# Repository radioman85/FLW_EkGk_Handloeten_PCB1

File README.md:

### Präsentation
[FabLab - Handlötkurs 02-2025.pdf](https://github.com/user-attachments/files/19078771/FabLab.-.Handlotkurs.02-2025.pdf)

### BOM

Currently unavailable

### Programming Pi Pico

## Preparation

1. Download, install and run the [thonny app](https://thonny.org/)
2. Connect the pico
3. In the Thonny app on the right bottom corner you can see your connected pico. From there install the micro python firmware

## Python Script
1. Once the pico has received its micro python firmware click on the "Stop" button on top of the thonny app.
5. Load the script you want to download to the raspi.
6. Go to "Save as", where it asks for either save on PC or on Raspberry (if not asked, the raspberry is not connected correctly (its firmware may not be up-to-date)).
7. Select "Raspberry Pi".
8. Save it as "main.py" (it must be named as "main" else it wont auto-start after reboot)
9. Happy running :-)

### Löten - Ausrüstung

 - Lötkolben (Link: [JBC CD-2BQF](https://shop.electronic-metals.ch/produkte/loettechnik/loetgeraete-ein-kanal/jbc/94951/jbc-kompakt-loetstation-cd-2bqf-wetec-edition?sPartner=10002?number=807278&gad_source=1&gclid=CjwKCAjwx-CyBhAqEiwAeOcTdfXDNTq5UXqakSejQxAiqUnyBB9TK4aIC8MYHQ78THFY60kKdBs1GRoCRy4QAvD_BwE), Handle (included): [T245](https://www.jbctools.com/t245-general-purpose-handle-product-45.html) , Spitzen (NOT included): [C245-030](https://shop.electronic-metals.ch/produkte/loettechnik/loet-entloetspitzen/jbc/c245-fuer-t245/rundform/8647/jbc-loetspitze-serie-c245-rundform?number=801290), -034, -906)
 - Lötzinn + Paste
    - 63% (Sn), 37% (Pb) (Link: [Lötdraht 0.7 mm](https://ch.farnell.com/multicore-loctite/d610scf222-250g/l-tdraht-60-40-0-7mm-250g/dp/454072), Link: [Paste - Chip Quik SMD291AX](https://ch.farnell.com/chip-quik/smd291ax/l-tpaste-no-clean-synthetisch/dp/3549310)) oder
    - 95,5% (Sn), 3,8% (Ag), 0,7% (Cu) (Link: [Lötdraht 0.7 mm](https://ch.farnell.com/multicore-loctite/d96scf222-250g/l-tdraht-105-0-7mm-250g/dp/454590), Link: [Chip Quik TS391SNL](https://ch.farnell.com/chip-quik/ts391snl/l-tpaste-no-clean-synthetisch/dp/3549323))
 - Lötflussmittel (Link: [Chip Quik SMD291](https://www.mouser.ch/ProductDetail/Chip-Quik/SMD291?qs=8BX3xQzFIvmwkympZqnNNA%3D%3D))
 - Lötmatte
 - Pinzetten (Link: [Weller Erem 7SASL, gebogen](https://ch.farnell.com/erem/7sasl/pr-zisionspinzette-gebogen-spitz/dp/2946763), Link: [Weller Erem 3SASL, gerade](https://ch.farnell.com/erem/3sasl/pinzette-120mm/dp/1014352))
 - Zahbüsrteli / Wattestäbli (Link: [M-Budget Zahnbürste](https://www.migros.ch/de/product/mo/96751))
 - Fläschli Isopropanol (Link: [Isopropanol 99,9 %](https://www.gerstaecker.ch/Isopropanol-99-9.html))
 - Shimblade (Link: [EDSYN - ST706](https://ch.farnell.com/edsyn/st706/halter-f-r-entl-tklingen/dp/844457), Ersatzklingen (Link: [EDSYN - RB641](https://ch.farnell.com/edsyn/rb641/entl-tklingen-zuschneidbares-stahlband/dp/844445))
 - Tip Tinner/Cleaner/Activator (Link: [Weller Tip Activater](https://www.simpex.ch/shop/produktionstechnik/loetzubehoer/tip-aktivator-bleifrei/?gad_campaignid=22242456144))

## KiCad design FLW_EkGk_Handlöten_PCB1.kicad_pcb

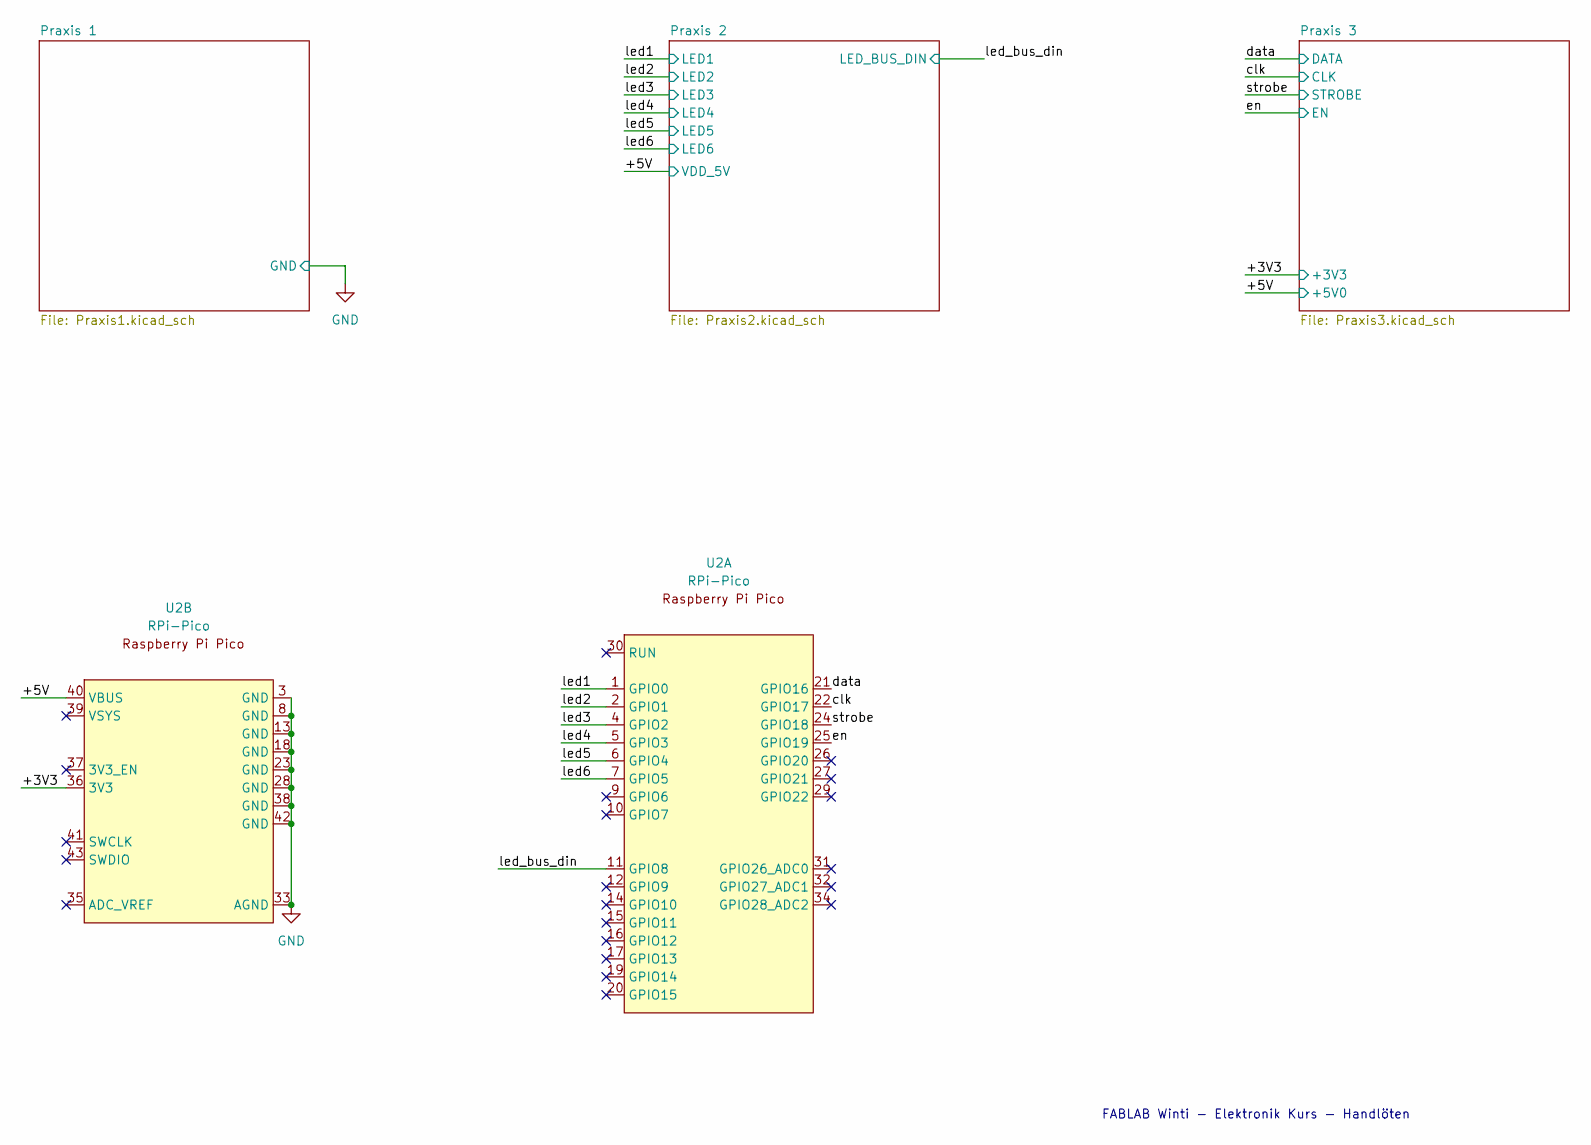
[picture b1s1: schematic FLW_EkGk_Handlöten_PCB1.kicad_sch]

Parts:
U2: RPi-Pico; RPi_Pico_SMD_TH

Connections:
/+3V3: U2.36 (3V3); also elsewhere on the board
/+5V: U2.40 (VBUS); also elsewhere on the board
/clk: U2.22 (GPIO17); also elsewhere on the board
/data: U2.21 (GPIO16); also elsewhere on the board
/en: U2.25 (GPIO19); also elsewhere on the board
/led1: U2.1 (GPIO0); also elsewhere on the board
/led2: U2.2 (GPIO1); also elsewhere on the board
/led3: U2.4 (GPIO2); also elsewhere on the board
/led4: U2.5 (GPIO3); also elsewhere on the board
/led5: U2.6 (GPIO4); also elsewhere on the board
/led6: U2.7 (GPIO5); also elsewhere on the board
/led_bus_din: U2.11 (GPIO8); also elsewhere on the board
/strobe: U2.24 (GPIO18); also elsewhere on the board
GND: U2.3 (GND), U2.8 (GND), U2.13 (GND), U2.18 (GND), U2.23 (GND), U2.28 (GND), U2.33 (AGND), U2.38 (GND), U2.42 (GND); also elsewhere on the board

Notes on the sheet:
FABLAB Winti - Elektronik Kurs - Handlöten

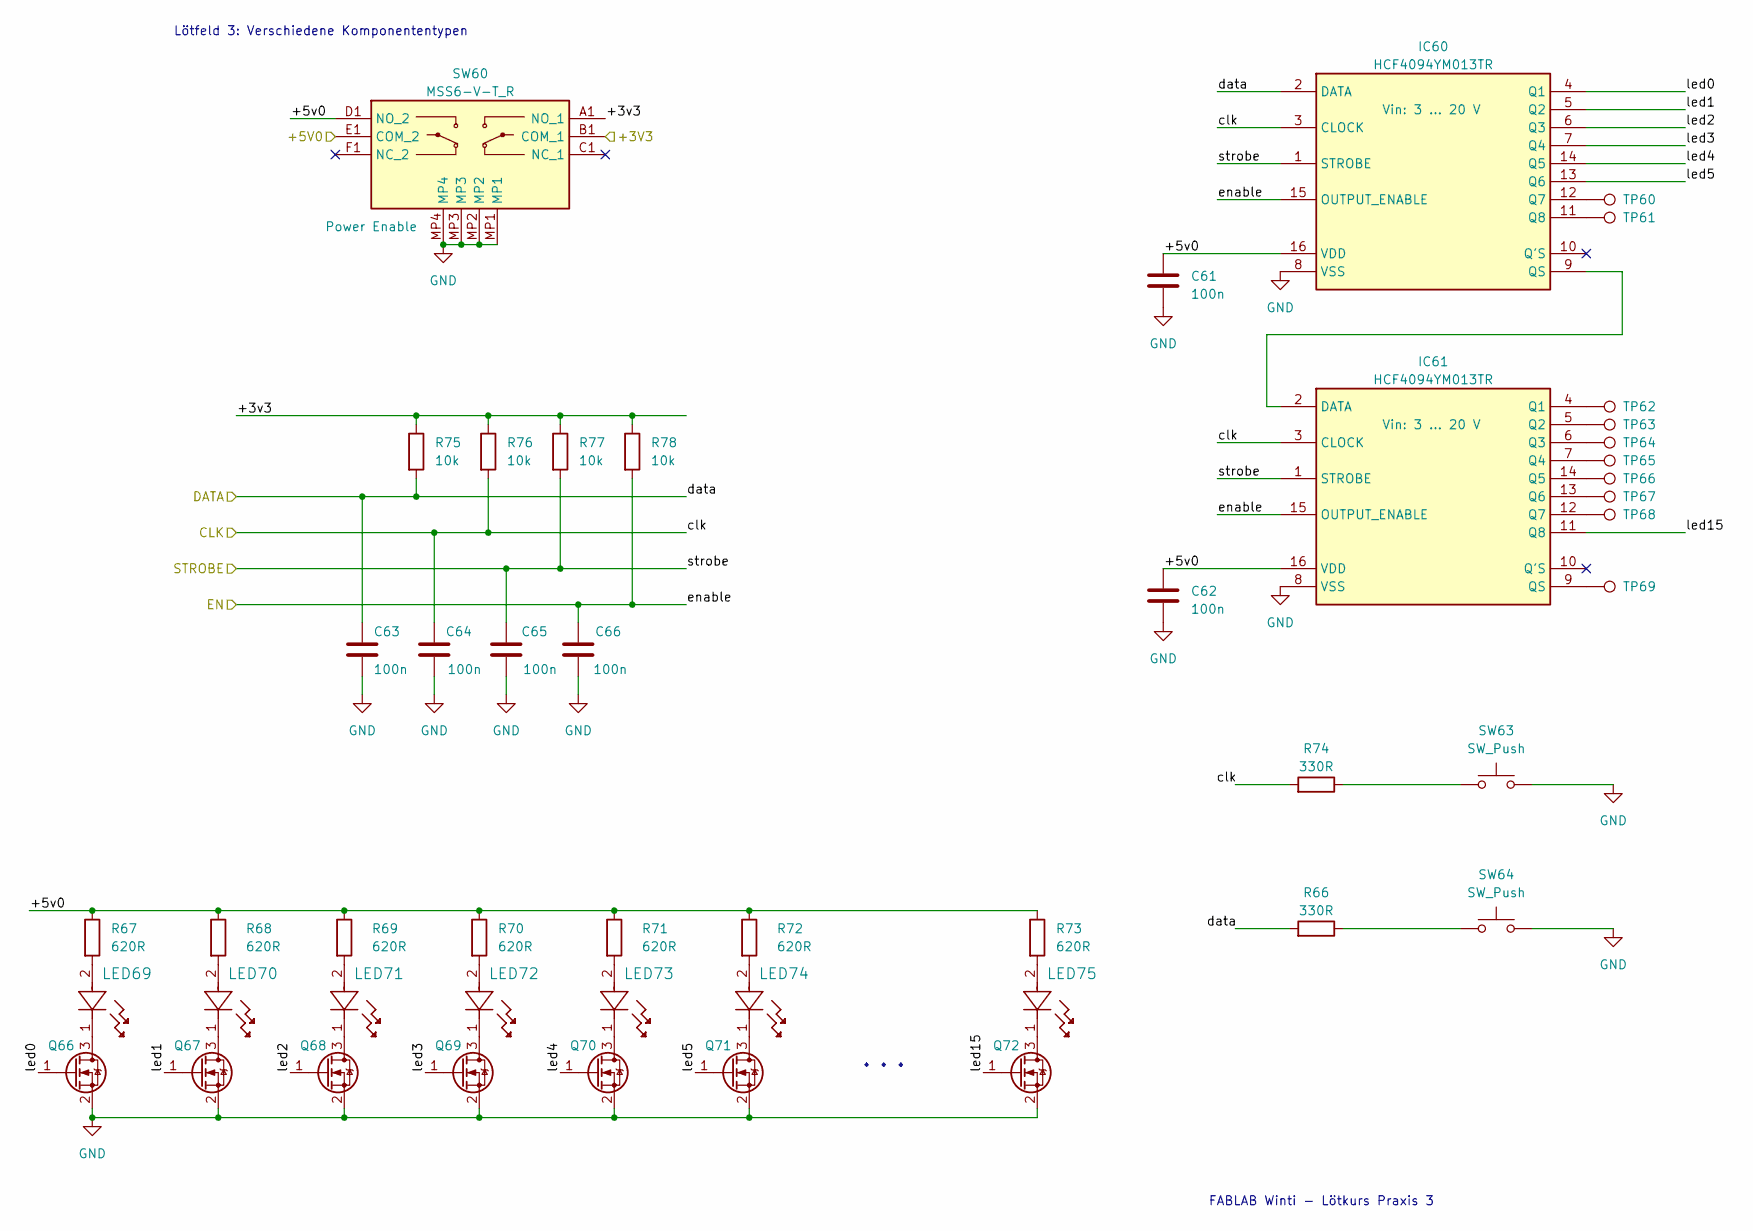
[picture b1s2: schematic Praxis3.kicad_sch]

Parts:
C61, C62, C63, C64, C65, C66: 100n; C_1206_3216Metric
IC60, IC61: HCF4094YM013TR; SOIC-16-SOIC127P600X175-16N; Voltage Vin: 3 ... 20 V; Mouser Part Number 511-HCF4094YM013TR
LED69, LED70, LED71, LED72, LED73, LED74, LED75: SML-LX1206SIC-TR; LED_SML-LX1206SIC-TR_LUM
Q66, Q67, Q68, Q69, Q70, Q71, Q72: 2N7002; SOT-23
R66, R74: 330R; R_1206_3216Metric
R67, R68, R69, R70, R71, R72, R73: 620R; R_1206_3216Metric
R75, R76, R77, R78: 10k; R_1206_3216Metric
SW60: MSS6-V-T_R; MSS6VTR; Mouser Part Number 113-MSS6-V-T/R
SW63, SW64: SW_Push; SW_Push_1P1T_NO_CK_KSC7xxJ
TP60, TP61, TP62, TP63, TP64, TP65, TP66, TP67, TP68, TP69: TestPoint; TestPointSimpleSMD

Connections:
/+3V3: SW60.B1 (COM_1); also elsewhere on the board
/+5V: SW60.E1 (COM_2); also elsewhere on the board
/Praxis 3/+3v3: R75.1, R76.1, R77.1, R78.1, SW60.A1 (NO_1)
/Praxis 3/+5v0: C61.1, C62.1, IC60.16 (VDD), IC61.16 (VDD), R67.1, R68.1, R69.1, R70.1, R71.1, R72.1, R73.1, SW60.D1 (NO_2)
/Praxis 3/led0: IC60.4 (Q1), Q66.1 (G)
/Praxis 3/led1: IC60.5 (Q2), Q67.1 (G)
/Praxis 3/led2: IC60.6 (Q3), Q68.1 (G)
/Praxis 3/led3: IC60.7 (Q4), Q69.1 (G)
/Praxis 3/led4: IC60.14 (Q5), Q70.1 (G)
/Praxis 3/led5: IC60.13 (Q6), Q71.1 (G)
/Praxis 3/led15: IC61.11 (Q8), Q72.1 (G)
/clk: C64.1, IC60.3 (CLOCK), IC61.3 (CLOCK), R74.2, R76.2; also elsewhere on the board
/data: C63.1, IC60.2 (DATA), R66.2, R75.2; also elsewhere on the board
/en: C66.1, IC60.15 (OUTPUT_ENABLE), IC61.15 (OUTPUT_ENABLE), R78.2; also elsewhere on the board
/strobe: C65.1, IC60.1 (STROBE), IC61.1 (STROBE), R77.2; also elsewhere on the board
GND: C61.2, C62.2, C63.2, C64.2, C65.2, C66.2, IC60.8 (VSS), IC61.8 (VSS), Q66.2 (S), Q67.2 (S), Q68.2 (S), Q69.2 (S), Q70.2 (S), Q71.2 (S), Q72.2 (S), SW60.MP1, SW60.MP2, SW60.MP3, SW60.MP4, SW63.2, SW64.2; also elsewhere on the board
unnamed: IC60.12 (Q7), TP60.1 (1_1)
unnamed: IC60.11 (Q8), TP61.1 (1_1)
unnamed: IC60.9 (QS), IC61.2 (DATA)
unnamed: IC61.4 (Q1), TP62.1 (1_1)
unnamed: IC61.5 (Q2), TP63.1 (1_1)
unnamed: IC61.6 (Q3), TP64.1 (1_1)
unnamed: IC61.7 (Q4), TP65.1 (1_1)
unnamed: IC61.14 (Q5), TP66.1 (1_1)
unnamed: IC61.13 (Q6), TP67.1 (1_1)
unnamed: IC61.12 (Q7), TP68.1 (1_1)
unnamed: IC61.9 (QS), TP69.1 (1_1)
unnamed: LED69.2, R67.2
unnamed: LED70.2, R68.2
unnamed: LED71.2, R69.2
unnamed: LED72.2, R70.2
unnamed: LED73.2, R71.2
unnamed: LED74.2, R72.2
unnamed: LED75.2, R73.2
unnamed: LED69.1, Q66.3 (D)
unnamed: LED70.1, Q67.3 (D)
unnamed: LED71.1, Q68.3 (D)
unnamed: LED72.1, Q69.3 (D)
unnamed: LED73.1, Q70.3 (D)
unnamed: LED74.1, Q71.3 (D)
unnamed: LED75.1, Q72.3 (D)
unnamed: R66.1, SW64.1
unnamed: R74.1, SW63.1

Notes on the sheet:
FABLAB Winti - Lötkurs Praxis 3
Lötfeld 3: Verschiedene Komponententypen
...

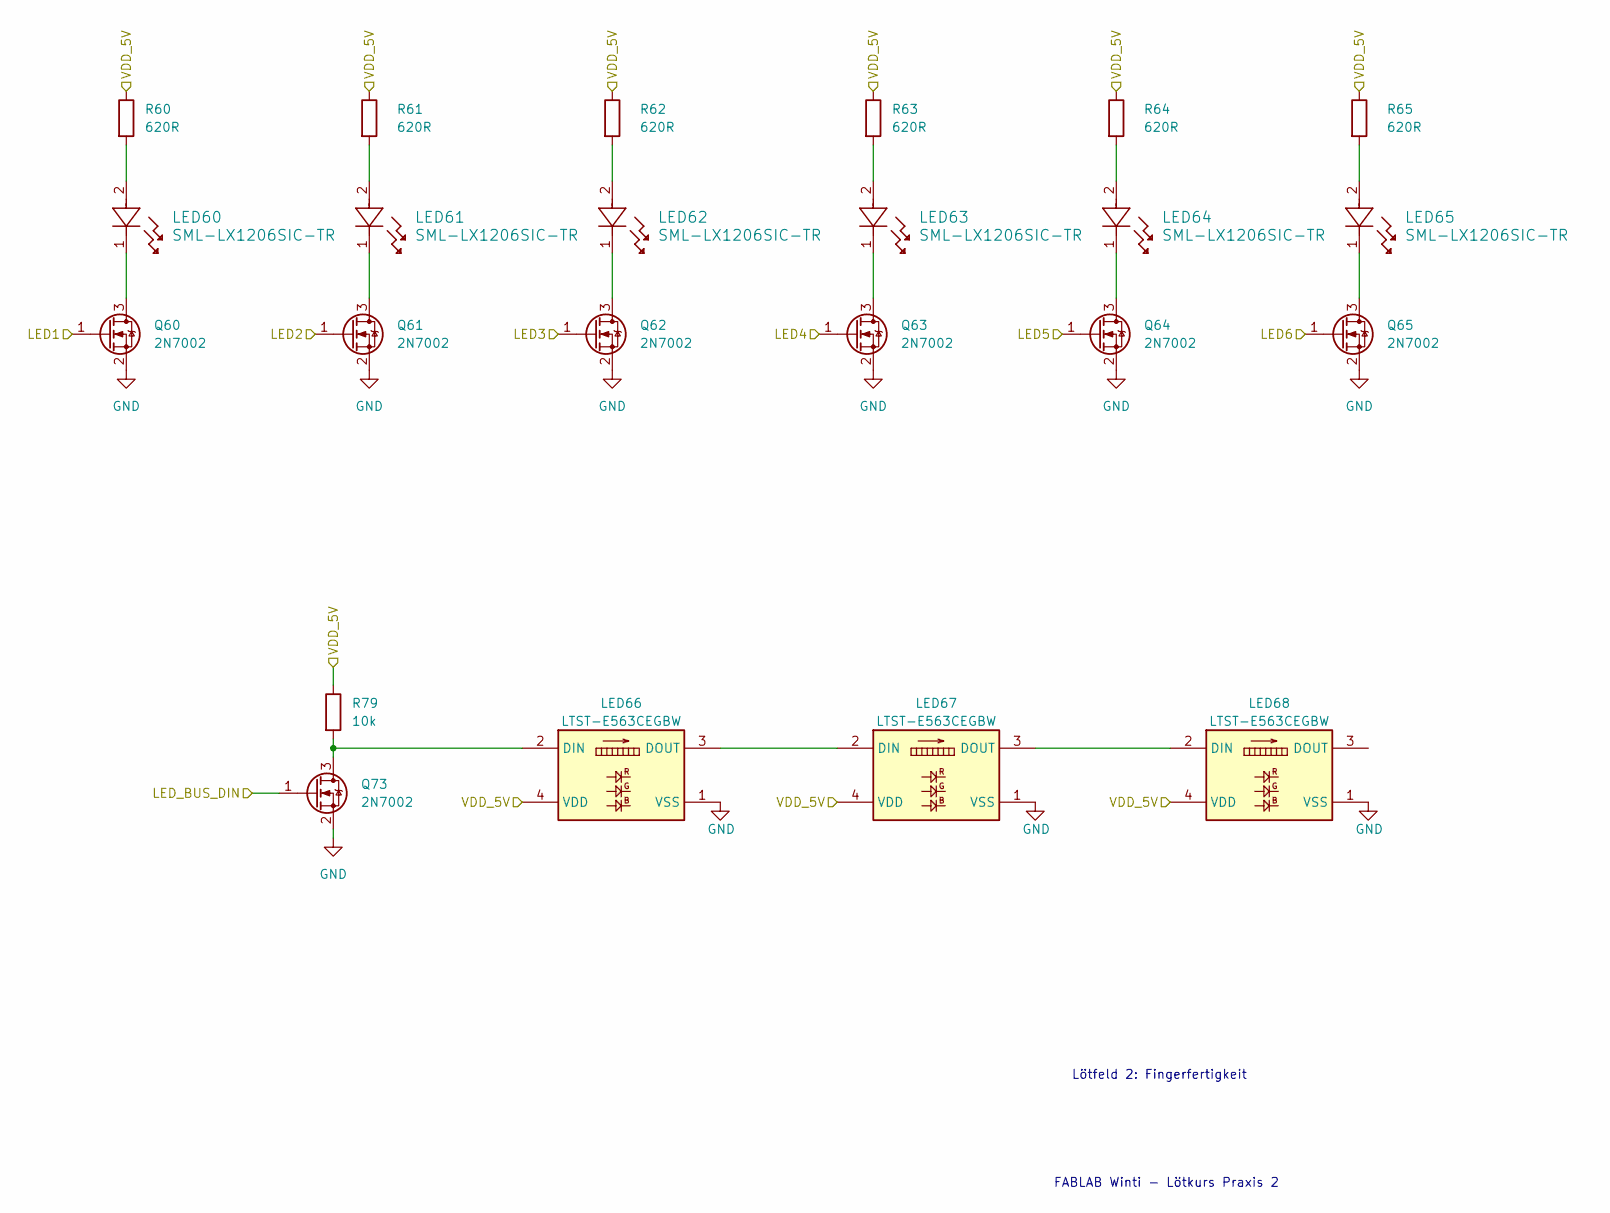
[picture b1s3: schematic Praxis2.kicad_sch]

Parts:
LED60, LED61, LED62, LED63, LED64, LED65: SML-LX1206SIC-TR; LED_SML-LX1206SIC-TR_LUM
LED66, LED67, LED68: LTST-E563CEGBW; LTSTE563CEGBW; Mouser Part Number 859-LTST-E563CEGBW
Q60, Q61, Q62, Q63, Q64, Q65, Q73: 2N7002; SOT-23
R60, R61, R62, R63, R64, R65: 620R; R_1206_3216Metric
R79: 10k; R_1206_3216Metric

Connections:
/+5V: LED66.4 (VDD), LED67.4 (VDD), LED68.4 (VDD), R60.1, R61.1, R62.1, R63.1, R64.1, R65.1, R79.1; also elsewhere on the board
/led1: Q60.1 (G); also elsewhere on the board
/led2: Q61.1 (G); also elsewhere on the board
/led3: Q62.1 (G); also elsewhere on the board
/led4: Q63.1 (G); also elsewhere on the board
/led5: Q64.1 (G); also elsewhere on the board
/led6: Q65.1 (G); also elsewhere on the board
/led_bus_din: Q73.1 (G); also elsewhere on the board
GND: LED66.1 (VSS), LED67.1 (VSS), LED68.1 (VSS), Q60.2 (S), Q61.2 (S), Q62.2 (S), Q63.2 (S), Q64.2 (S), Q65.2 (S), Q73.2 (S); also elsewhere on the board
unnamed: LED60.2, R60.2
unnamed: LED61.2, R61.2
unnamed: LED62.2, R62.2
unnamed: LED63.2, R63.2
unnamed: LED64.2, R64.2
unnamed: LED65.2, R65.2
unnamed: LED66.2 (DIN), Q73.3 (D), R79.2
unnamed: LED66.3 (DOUT), LED67.2 (DIN)
unnamed: LED67.3 (DOUT), LED68.2 (DIN)
unnamed: LED60.1, Q60.3 (D)
unnamed: LED61.1, Q61.3 (D)
unnamed: LED62.1, Q62.3 (D)
unnamed: LED63.1, Q63.3 (D)
unnamed: LED64.1, Q64.3 (D)
unnamed: LED65.1, Q65.3 (D)

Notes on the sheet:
Lötfeld 2: Fingerfertigkeit
FABLAB Winti - Lötkurs Praxis 2

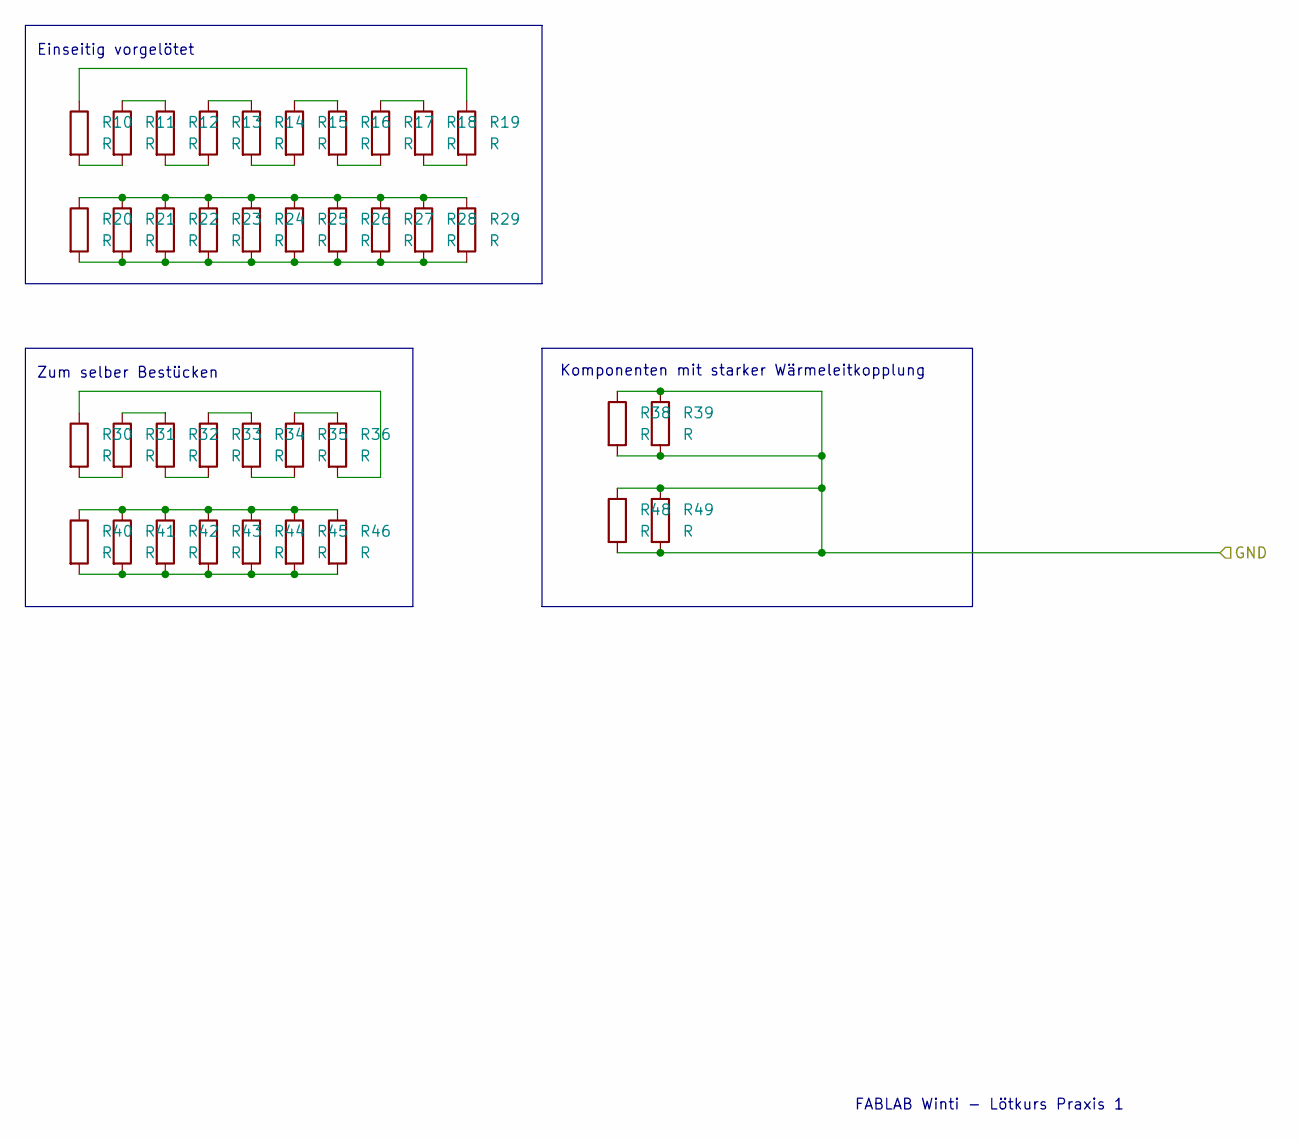
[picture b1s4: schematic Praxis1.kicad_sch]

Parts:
R10, R11, R12, R13, R14, R15, R16, R17, R18, R19, R30, R31, R32, R33, R34, R35, R36, R38, R39: R; R_1206_3216Metric
R20, R21, R22, R23, R24, R25, R26, R27, R28, R29, R40, R41, R42, R43, R44, R45, R46, R48, R49: R; R_0805_2012Metric

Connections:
GND: R38.1, R38.2, R39.1, R39.2, R48.1, R48.2, R49.1, R49.2; also elsewhere on the board
unnamed: R10.1, R19.1
unnamed: R10.2, R11.2
unnamed: R11.1, R12.1
unnamed: R12.2, R13.2
unnamed: R13.1, R14.1
unnamed: R14.2, R15.2
unnamed: R15.1, R16.1
unnamed: R16.2, R17.2
unnamed: R17.1, R18.1
unnamed: R18.2, R19.2
unnamed: R20.1, R21.1, R22.1, R23.1, R24.1, R25.1, R26.1, R27.1, R28.1, R29.1
unnamed: R20.2, R21.2, R22.2, R23.2, R24.2, R25.2, R26.2, R27.2, R28.2, R29.2
unnamed: R30.1, R36.2
unnamed: R30.2, R31.2
unnamed: R31.1, R32.1
unnamed: R32.2, R33.2
unnamed: R33.1, R34.1
unnamed: R34.2, R35.2
unnamed: R35.1, R36.1
unnamed: R40.1, R41.1, R42.1, R43.1, R44.1, R45.1, R46.1
unnamed: R40.2, R41.2, R42.2, R43.2, R44.2, R45.2, R46.2

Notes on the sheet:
Einseitig vorgelötet
Komponenten mit starker Wärmeleitkopplung
FABLAB Winti - Lötkurs Praxis 1
Zum selber Bestücken

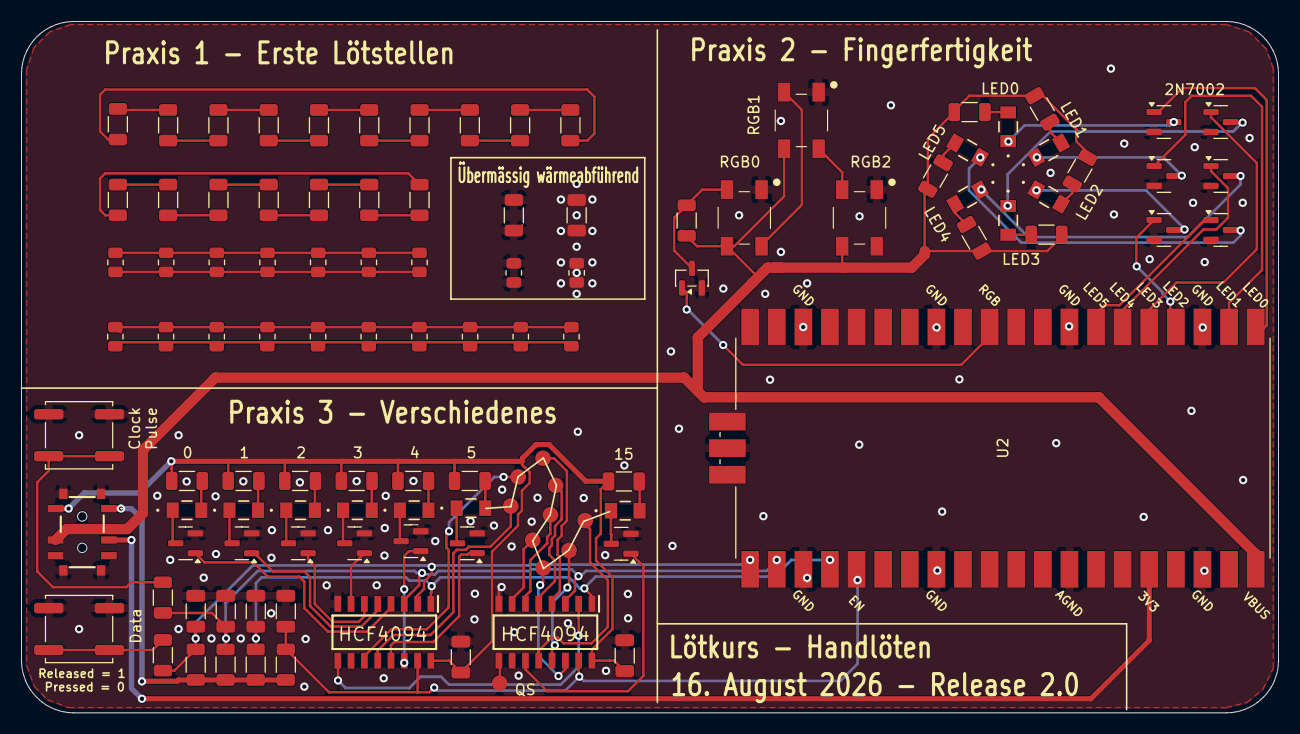
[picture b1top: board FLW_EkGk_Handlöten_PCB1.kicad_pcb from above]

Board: 2 copper layers, 120.0 x 66.0 mm, 110 parts (0 on the bottom side), 86 nets.

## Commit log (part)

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2023-09-23 asdf
    asdf
2023-09-24 continued
2023-10-24 improved
2023-11-06 Almost finished
2023-11-06 Cleaned up some warnings
2023-11-21 Removed Aisler Tag
2023-11-21 Last changes
2024-02-29 cleanup
2024-02-29 Resolves #1: increased footprint solder mask to get better access with the solder tip
2024-03-01 Resolves #2: Added current limiting resistor values (i.e. 620 Ohm)
2024-05-28 added p-touch labels
2024-05-31 updated BOM-Ptouch Etikett, added 620R
2024-08-04 Create PicoBlinkExample.py
    Added example script in micro python
2024-08-07 asdf
2024-09-02 Resolves #3: Missing Pin Marks
2025-03-04 Added Presentation (PDF)
2025-03-04 Added Soldering Equipment
2026-01-13 Added C for all digital signals
2026-04-08 update to kicad 10
